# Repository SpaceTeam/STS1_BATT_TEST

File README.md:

# STS1_BATT_TEST
This repository contains a KiCAD design, that allows automated testing of battery cells.

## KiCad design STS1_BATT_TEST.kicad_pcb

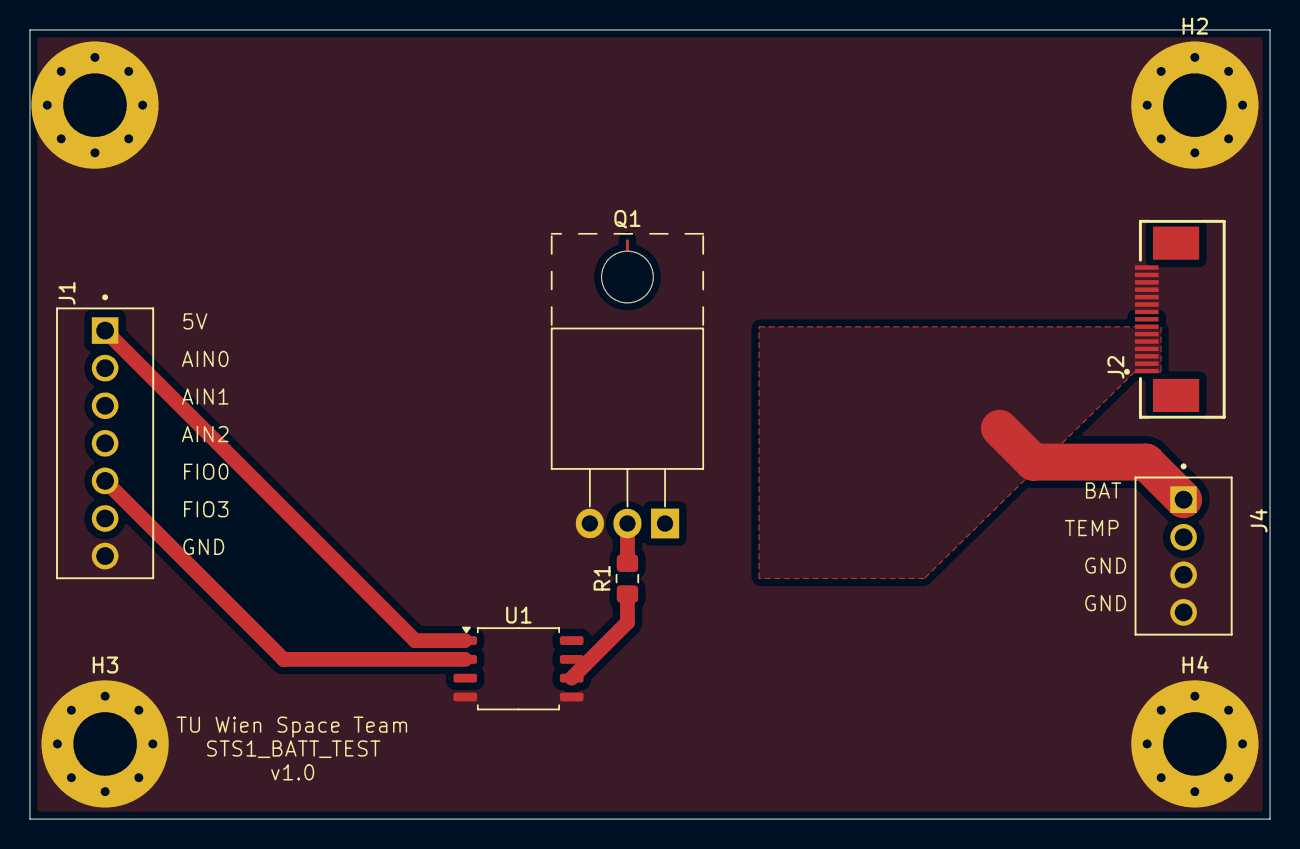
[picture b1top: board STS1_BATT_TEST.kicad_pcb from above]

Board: 2 copper layers, 83.8 x 53.3 mm, 10 parts (0 on the bottom side), 8 nets.

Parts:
H1, H2, H3, H4: MountingHole_Pad; MountingHole_4.3mm_M4_Pad_Via
J1: TE 282834-6; TE_282834-7
J2: Conn_01x15; SAMTEC_ZF5S-15-01-T-WT-K-TR
J4: Conn_01x04; TE_282834-4
Q1: IPP050N03LF2S; TO-220-3_Horizontal_TabUp
R1: 100; C_0805_2012Metric_Pad1.18x1.45mm_HandSolder
U1: TC4420VOA713; SOIC-8_5.275x5.275mm_P1.27mm

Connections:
+5V: J1.1, U1.1 (VDD), U1.8 (VDD)
/AIN0: J1.2, J2.1, J2.2, J2.3, J2.4, J2.5, J2.6, J2.7, J4.1
/AIN1: J1.3, Q1.1 (D)
/FIO0: J1.5, U1.2 (Input)
/Load Mosfet with cooling/GATE: R1.1, U1.6 (Output), U1.7 (Output)
/TEMP: J2.8, J4.2
GND: H1.1, H2.1, H3.1, H4.1, J1.7, J2.9, J2.10, J2.11, J2.12, J2.13, J2.14, J2.15, J4.3, J4.4, Q1.3 (S), U1.4 (GND), U1.5 (GND)
unnamed: Q1.2 (G), R1.2

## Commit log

2025-03-16 Added scafolding.
2025-03-16 Fixed connectors.
2025-03-17 Added discharge Mosfet.
2025-03-24 Prepared STS1_BATT_TEST.
2025-03-24 Added dummy python script.
2025-03-24 Added dummy python script. (#1)
